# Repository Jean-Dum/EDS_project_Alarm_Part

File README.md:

# EDS_project_Alarm_Project

## Motion detection alarm

## Principal Equipment

	- PIR Sensor               --> EKMC1601111 - Motion sensor 5m 94°, Panasonic
	
	- Electromechanical Buzzer --> kmtg1603 

	- Button (For alarm test)  --> https://www.elfa.se/en/tactile-switch-pts-1no-160gf-6mm-pts645sm43smtr92lfs/p/30119498?origPos=40&q=smd%20button&pos=5&origPageSize=10&track=true

	- Variable resistor (for smoke sensor) --> https://www.elfa.se/en/trimmer-potentiometer-kohm-250-mw-bi-technologies-23br1klftr/p/16432066?q=*&pos=3&origPos=255&origPageSize=10&track=true&fbclid=IwAR1p6efSrgXudRJqt7ZX97Rhud_PuTN6X5KsHpLk5Swx5VFpF2Jh6Jaqm8U
	
	- LoRa module (long range low-power wide-area network technology) --> Murata CMWX1ZZABZ

	- Smoke Sensor --> HS-131 https://www.elfa.se/en/gas-sensor-sencera-co-ltd-hs-131/p/17302706?q=smoke+detector&pos=10&origPos=23&origPageSize=100&track=true

### Desired features

The main idea is to build a system which can detect the movement of a person using a PIR sensor. This movement will trigger an alarm and communicate using LoRa to another MCU managed by our associated team. The only way of desactivate the alarm is to introduce the correct code in the second team's terminal.

The system will also include a buzzer and a test button.

### Obtained features

Our PCB is now able to detect the movements up to 4 meters away. It makes the buzzer ring and to stop it you just have to press the button on the PCB.

At the programm beginning there is 10 seconds of waiting in order to wait for the user to go away (otherwise it will disrupt the sensor calibration) during which the info LED is blinking. Then there is 10 seconds of sensor calibration, in which it makes a 40 samples average to make a reference value and makes the LED blinking faster.

Then the programm runs and the buzzer will ring only if the sensor value exceeds the reference value.

If the alarm is stopped by pressing the button, to reactivate it just press again the buttton, the software will again wait 10 seconds to let the user go away to avoid the buzzer to ring immediatly and then run motion detection again. During this time the info LED is blinking again.

Our system send a '1' by serial connection when the sensor is triggered. The alarm can be turned off by serial connection if it receive a '1' but to do so you have to uncomment lines 143 to 152 and build the code again.

#### Here is a diagram of our program:

## Run project

### Hardawre

- Connect the St-Link programmer from the nucleo board to the PCB. To do so just connect the SWD pins to the programming pins of our PCB, in the same order.
- Then verify that the nucleo St-Link programmer wont programm the nucleo board but our PCB. To do so remove the St-Link programmer and nucleo board connectors and remove the connector that power the nucleo board.
- Then connect both the St-Link programmer and PCB USB to your computer.

### Software
Open a terminal
#### Packages installation
- First of all install openocd:
> sudo apt-get install openocd
- install cargo:
> sudo apt-get install cargo
- install arm-none-eabi-gdb:
> sudo apt-get install arm-none-eabi-gdb
- Update rust tools:
> rustup update
> rustup target add thumbv7em-none-eabihf

#### Build software
> cargo build --release

#### Run software
- Clone this repo on your computer:
> git clone https://github.com/Jean-Dum/EDS_project_Alarm_Part.git
- Then go in the software directory:
> cd EDS_project_Alarm_Part/Software/
- Execute openocd software:
> openocd -f openocd.cfg
- Open a new terminal (in the same directory) and run the code:
> cargo build --release
- Now you are in the GDB interface, just type "c" and press two times enter key. You can look the code output in the openocd terminal.

## Possible Extras

If everything goes on time and we do not have any big difficulties in the project, we plan to add also some kind of smoke detector so the alarm system is more complete. 

We also thought of adding a fingerprint sensor for desactivating the alarm in the detector terminal.

## Limitations

The fact of working two groups together makes the communication between terminals harder but we dont expect any other big problem in our terminal.

The main limitation was that there few informations about Rust (and especially about the stm32L0) on internet, doing our researchs to resolve our problems was really difficult.

## Design and Electronic

We design our circuit using Kicad and testing some parts of the circuit in LTspice.  

### Some facts about the circuit
	
- Three different LEDs: one to get infos on the code execution, one for the power and one connected to the buzzer.
	
- We add a different voltage regulator (LT1117) that allows us to have 3.3v always without the need of resistors for adjustment of the output, so we reduces the space used.

- For the Smoke detector we used a potentiometer we can use for changing the output, this is because the detector can work on different environments (humidity, temperature...) and we need to adjust the potentiometer to have an ideal output.

### Layout

For the layout we tried to make the PCB as small as possible so it can fit in a small case and this way the detection system will be more inconspicuous.

All the components are on the same layer (top) but the PIR, this way we have more space and a better 'view' for the motion sensor. The connectors are all placed on the sides of the board so it is easier to use them. We tried to put the buzzer as far as possible from the MCU just incase the vibrations of the buzzer can make any damage on the small soldering pads of the MCU in a large period of time, the decoupling capacitors and sensors are placed as close as possible from the MCU.

### Testing

We did some different tests on the board before and after ordering it
- We used LTspice to make sure everything was okey
- Test for short-circuits and bad connections
- Test after soldering the MCU
- For short-circuits between pads (here we detected a problem)
- For voltage reverse to make sure all the pads were connected
- We tested the MCU by connecting it at a low current
- Test the final performance 

## Issues / Problems 

- Circuit
	- The LT1117 pins of the footprint where wrong (they were saved as if it was LM1117) so we had to make a small fix

- Layout and soldering
	- We had to apply the re-flow process twice because of a lack of flux in the first re-flow but finally applying more flux and doing the process again we managed to solder it perfect.

- Programming
	- It took us some time to manage to connect the PCB and didn't succeed to use vscode to run our code.
	- We made a mistake on the pins connection: The PA4 pin (used for the buzzer) don't generate PWM, we had to add a wire between the PA4 and PA3 pins because PA3 can generate PWM and is used for the smoke sensor, which is not used.
	- We didn't succeed to use the Lora module, by lack of time and because this one is way to complicated to use.
	- All the programming part was really complicated to realise, in fact there is not a lot of things about rust and espetially with the stm32L0 on internet, resolving our issues was a real struggle.

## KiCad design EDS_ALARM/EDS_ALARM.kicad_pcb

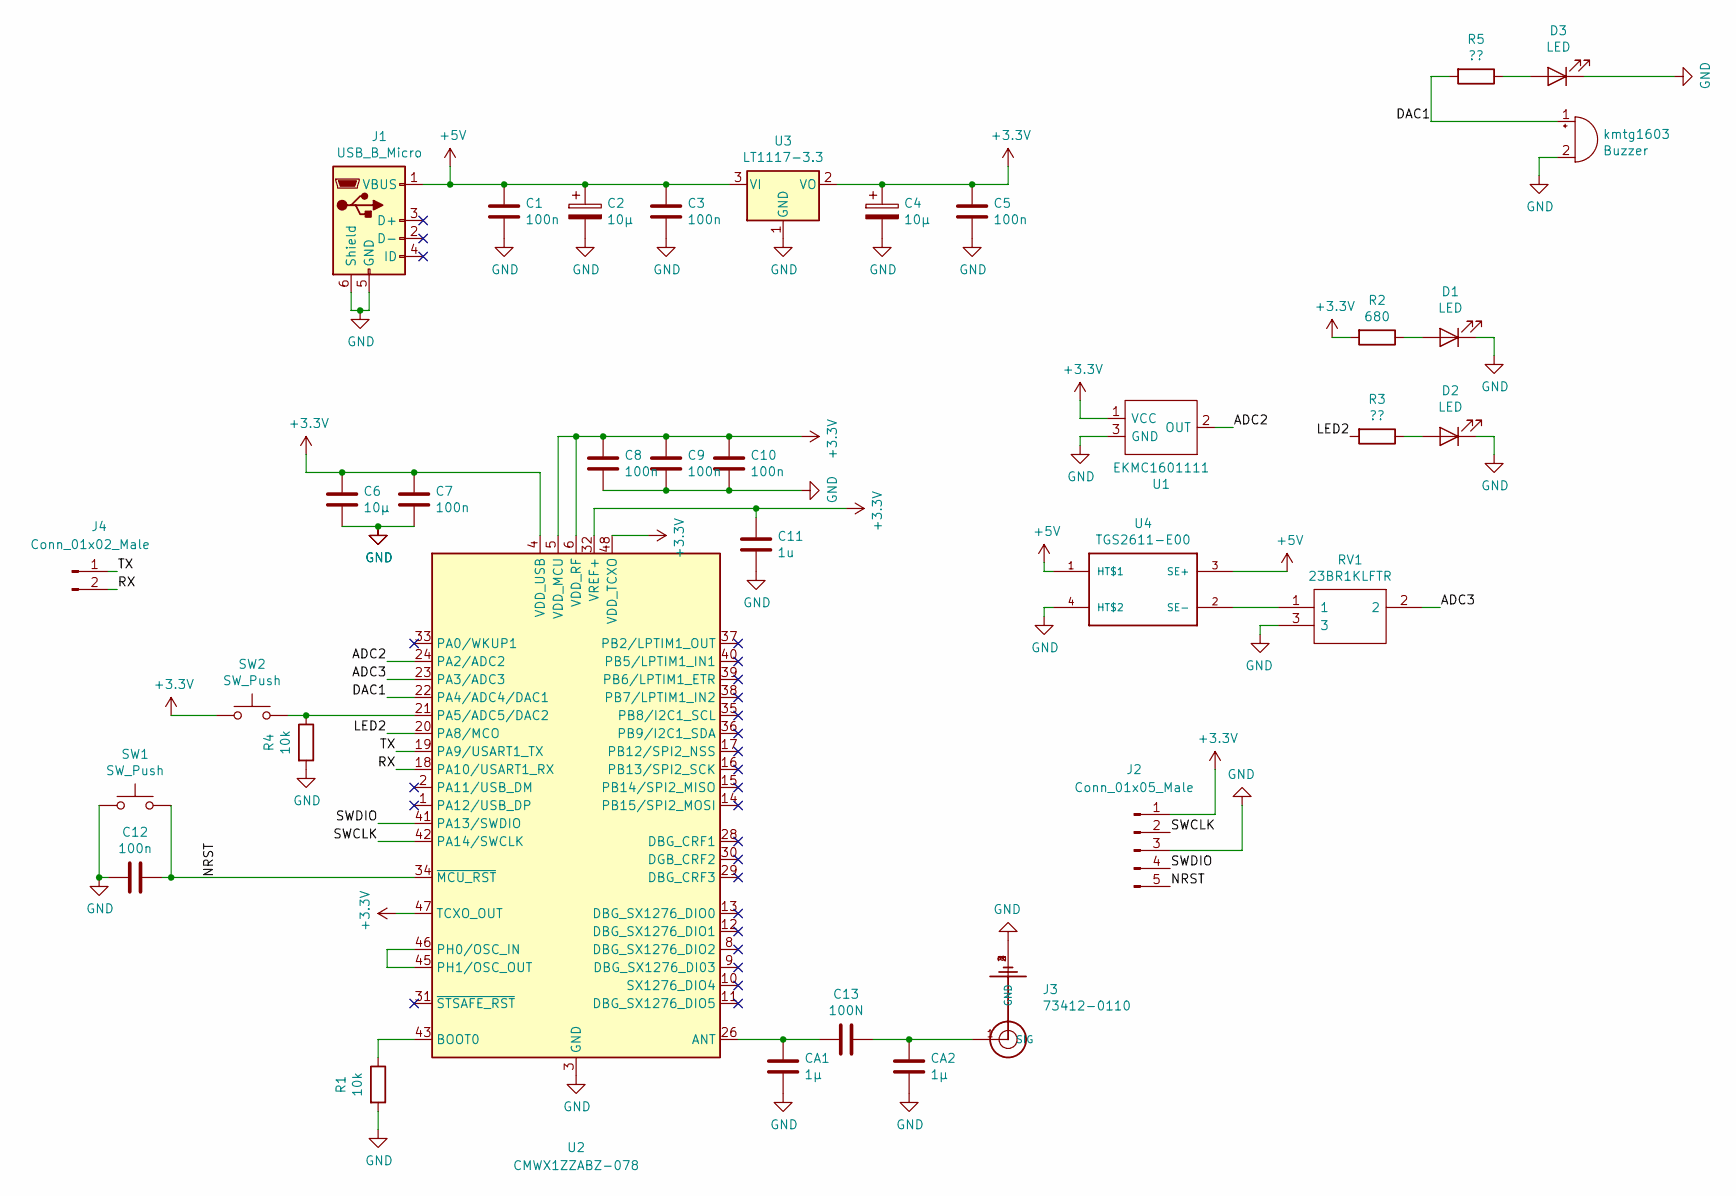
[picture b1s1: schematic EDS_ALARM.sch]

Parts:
C1, C3, C5, C7, C8, C9, C10, C12: 100n; C_0805_2012Metric_Pad1.15x1.40mm_HandSolder
C2, C4: 10µ; CP_Elec_5x4.4
C6: 10µ; C_0805_2012Metric_Pad1.15x1.40mm_HandSolder
C11: 1u; C_0805_2012Metric_Pad1.15x1.40mm_HandSolder
C13: 100N; C_0805_2012Metric_Pad1.15x1.40mm_HandSolder
CA1, CA2: 1µ; C_0805_2012Metric_Pad1.15x1.40mm_HandSolder
D1, D2, D3: LED; LED_0805_2012Metric
J1: USB_B_Micro; USB_Micro-B_Wuerth_629105150521
J2: Conn_01x05_Male; PinSocket_1x05_P2.54mm_Vertical
J3: 73412-0110; U.FL_Molex_MCRF_73412-0110_Vertical
J4: Conn_01x02_Male; PinSocket_1x02_P2.54mm_Vertical
R1, R4: 10k; R_0805_2012Metric_Pad1.15x1.40mm_HandSolder
R2: 680; R_0805_2012Metric_Pad1.15x1.40mm_HandSolder
R3, R5: ??; R_0805_2012Metric_Pad1.15x1.40mm_HandSolder
RV1: 23BR1KLFTR; 23B_1; Manufacturer_Part_Number 23BR1KLFTR; Mouser Part Number 858-23BR1KLFTR
SW1, SW2: SW_Push; SW_SPST_PTS645
U1: EKMC1601111; VZ-STANDARD; Manufacturer_Part_Number EKMC1601111; Mouser Part Number 769-EKMC1601111
U2: CMWX1ZZABZ-078; CMWX1ZZABZ_NEW
U3: LT1117-3.3; SOT-223
U4: TGS2611-E00; TGS2611C00
kmtg1603: Buzzer; KMTG16031

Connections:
+3V3: C4.1, C5.1, C6.1, C7.1, C8.1, C9.1, C10.1, C11.1, J2.1, R2.2, SW2.1, U1.1 (VCC), U2.4 (VDD_USB), U2.5 (VDD_MCU), U2.6 (VDD_RF), U2.32 (VREF+), U2.47 (TCXO_OUT), U2.48 (VDD_TCXO), U3.2 (VO)
+5V: C1.1, C2.1, C3.1, J1.1 (VBUS), U3.3 (VI), U4.1 (HT$1), U4.3 (SE+)
/ADC2: U1.2 (OUT), U2.24 (PA2/ADC2)
/ADC3: RV1.2, U2.23 (PA3/ADC3)
/DAC1: R5.2, U2.22 (PA4/ADC4/DAC1), kmtg1603.1 (-)
/LED2: R3.2, U2.20 (PA8/MCO)
/NRST: C12.1, J2.5, SW1.2, U2.34 (~MCU_RST)
/RX: J4.2, U2.18 (PA10/USART1_RX)
/SWCLK: J2.2, U2.42 (PA14/SWCLK)
/SWDIO: J2.4, U2.41 (PA13/SWDIO)
/TX: J4.1, U2.19 (PA9/USART1_TX)
GND: C1.2, C2.2, C3.2, C4.2, C5.2, C6.2, C7.2, C8.2, C9.2, C10.2, C11.2, C12.2, CA1.2, CA2.2, D1.1 (K), D2.1 (K), D3.1 (K), J1.5 (GND), J1.6 (Shield), J2.3, J3.2 (GND), J3.3 (GND), J3.4 (GND), R1.2, R4.2, RV1.3, SW1.1, U1.3 (GND), U2.3 (GND), U2.7 (GND), U2.25 (GND), U2.27 (GND), U2.44 (GND), U2.49 (GND), U2.50 (GND), U2.51 (GND), U2.52 (GND), U2.53 (GND), U2.54 (GND), U2.55 (GND), U2.56 (GND), U2.57 (GND), U3.1 (GND), U4.4 (HT$2), kmtg1603.2 (+)
unnamed: C13.1, CA2.1, J3.1 (SIG)
unnamed: C13.2, CA1.1, U2.26 (ANT)
unnamed: D1.2 (A), R2.1
unnamed: D2.2 (A), R3.1
unnamed: D3.2 (A), R5.1
unnamed: R1.1, U2.43 (BOOT0)
unnamed: R4.1, SW2.2, U2.21 (PA5/ADC5/DAC2)
unnamed: RV1.1, U4.2 (SE-)
unnamed: U2.45 (PH1/OSC_OUT), U2.46 (PH0/OSC_IN)

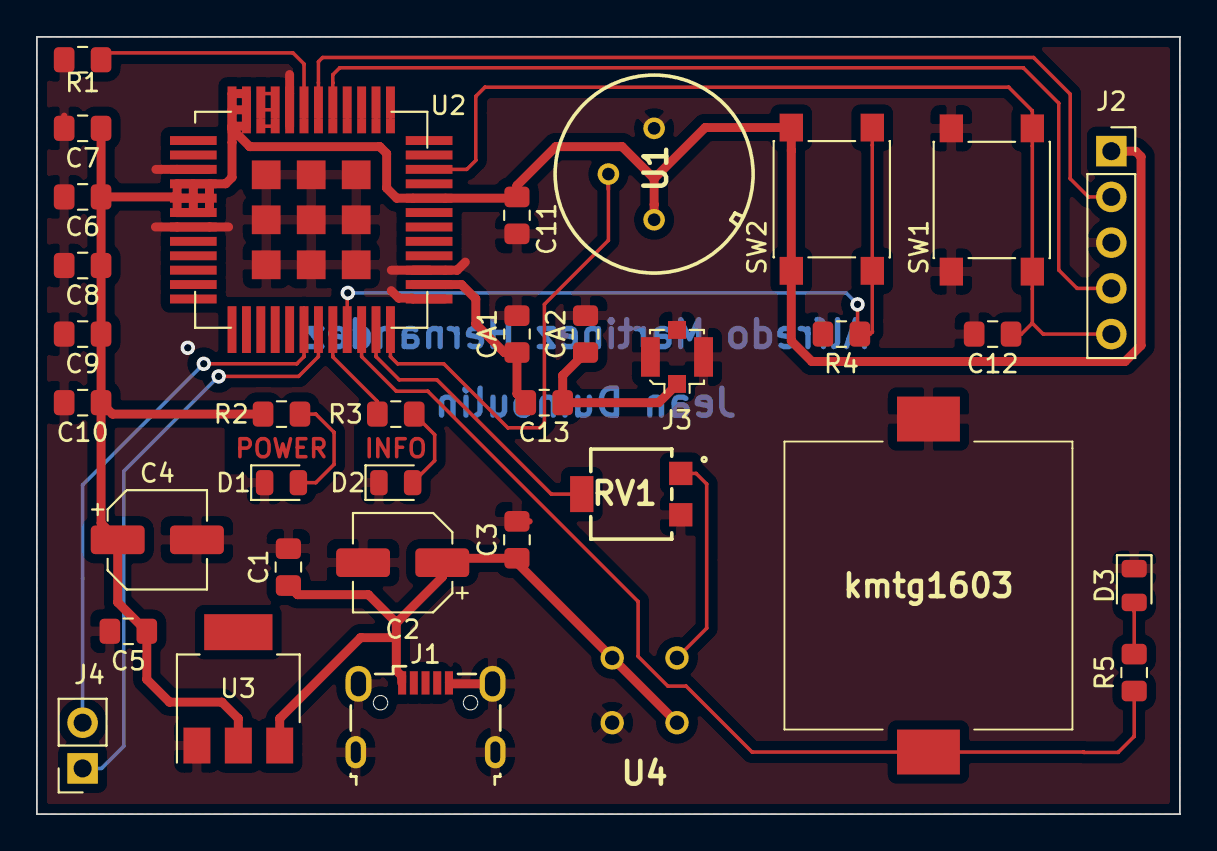
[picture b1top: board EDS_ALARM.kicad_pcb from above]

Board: 2 copper layers, 63.5 x 43.2 mm, 35 parts (0 on the bottom side), 21 nets.

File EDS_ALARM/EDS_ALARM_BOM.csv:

"Id";"Identificador";"Empaquetado";"Cantidad";"Identificación";"Suministrador y ref";
1;"C1,C3,C5,C7,C8,C9,C10,C12";"C_0805_2012Metric_Pad1.15x1.40mm_HandSolder";8;"100n";;;
2;"C2,C4";"CP_Elec_5x4.4";2;"10µ";;;
3;"C6";"C_0805_2012Metric_Pad1.15x1.40mm_HandSolder";1;"10µ";;;
4;"C11";"C_0805_2012Metric_Pad1.15x1.40mm_HandSolder";1;"1u";;;
5;"C13";"C_0805_2012Metric_Pad1.15x1.40mm_HandSolder";1;"100N";;;
6;"CA1,CA2";"C_0805_2012Metric_Pad1.15x1.40mm_HandSolder";2;"1µ";;;
7;"J1";"USB_Mini-B_Lumberg_2486_01_Horizontal";1;"USB_B_Micro";;;
8;"J2";"PinHeader_1x06_P2.54mm_Vertical";1;"Conn_01x06_Male";;;
9;"J3";"U.FL_Molex_MCRF_73412-0110_Vertical";1;"73412-0110";;;
10;"R1";"R_0805_2012Metric_Pad1.15x1.40mm_HandSolder";1;"10k";;;
11;"U2";"CMWX1ZZABZ";1;"CMWX1ZZABZ-078";;;
12;"U3";"SOT-223";1;"LT1117-3.3";;;
13;"U1";"VZ-STANDARD";1;"EKMC1601111";;;
14;"D1,D2";"LED_0805_2012Metric";2;"LED";;;
15;"RV1";"23B_1";1;"23BR1KLFTR";;;
16;"SW1";"SW_SPST_PTS645";1;"SW_Push";;;
17;"kmtg1603";"KMTG16031";1;"Buzzer";;;
18;"U4";"TGS2611C00";1;"TGS2611-E00";;;

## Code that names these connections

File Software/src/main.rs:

// Made by Jean Dumoulin and Alfredo Martinez Hernandez
// This code is meant to ring the alarm when the PIR sensor detects movement next to it

#![no_main]
#![no_std]
#![allow(non_snake_case)] 
#![deny(unsafe_code)]
#![deny(warnings)]

extern crate panic_halt;

use cortex_m_rt::entry;
use cortex_m_semihosting::{hprintln, hprint};
use stm32l0xx_hal::{self, pac, pwm, prelude::*, rcc::Config, serial};
// use nb::block; Uncomment if serial input is used

extern crate cortex_m;

#[entry]
fn main() -> ! {
    hprintln!("\nBeginning initialization").unwrap();

    let dp = pac::Peripherals::take().unwrap();
    let cp = cortex_m::Peripherals::take().unwrap();

    // Configure the clock.
    let mut rcc = dp.RCC.freeze(Config::hsi16());

    // Get the delay provider.
    let mut delay = cp.SYST.delay(rcc.clocks);

    // Acquire the GPIOA peripheral. This also enables the clock for GPIOA in the RCC register.
    let gpioa = dp.GPIOA.split(&mut rcc);

    // Configure PA8 as output (info LED output)
    let mut infoLED = gpioa.pa8.into_push_pull_output();

    // Configure PA5 as input (SW2)
    let button = gpioa.pa5.into_push_pull_output();
    
    // Configure the timer as PWM on PA3 (connected to PA4)
    let pwm = pwm::Timer::new(dp.TIM2, 1.khz(), &mut rcc);
    let mut pwm = pwm.channel4.assign(gpioa.pa3);
    let max_duty = pwm.get_max_duty() / 4095;
    pwm.enable();
    
    // Configure ADC on PA2
    let mut adc = dp.ADC.constrain(&mut rcc);
    let mut a2 = gpioa.pa2.into_analog();

    // Configure the serial peripheral on pa9 and pa10
    let tx_pin = gpioa.pa9;
    let rx_pin = gpioa.pa10;
    let serial = dp
        .USART1
        .usart((tx_pin, rx_pin), serial::Config::default(), &mut rcc)
        .unwrap();
    let (mut tx, _rx) = serial.split();

    // Initialize PIR reference value to 0
    let mut PIR_ref:u16 = 0;

    // Initialize the alarm activation boolean
    let mut alarmOnOff = true;

    // 5 seconds pause, indicates to the user that he must move away to avoid an immediate ringing
    for x in 0..10 {
        hprint!("\rWait {}s", 4 - x/2).unwrap();
        // Blink the info LED: 250ms OFF, 250ms ON
        delay.delay(250.ms());
        infoLED.set_low().unwrap();
        delay.delay(250.ms());
        infoLED.set_high().unwrap();
    }
    // Print new line
    hprintln!("").unwrap();
    // 5 seconds initialization time, makes the sum of 20 samples
    for x in 0..20 {
        hprint!("\rCalibration: {}s", 4 - x/4).unwrap();
        // Sum a PIR ADC sample
        PIR_ref = PIR_ref.wrapping_add(adc.read(&mut a2).unwrap());
        // Blink the info LED: 125ms OFF, 125ms ON
        delay.delay(125.ms());
        infoLED.set_low().unwrap();
        delay.delay(125.ms());
        infoLED.set_high().unwrap();
    }

    // Divide the result of the sum by 20, the result of the average is doubled
    let PIR_ref: u16 = PIR_ref/10;
    // Prints the average result
    hprintln!("\nReference value: {}\n", PIR_ref).unwrap();

    loop {
        // If the button is pushed
        if button.is_high().unwrap(){
            // Wait until the button is released
            while button.is_high().unwrap(){ 
                // Wait 200ms to avoid rebounce
                delay.delay(200.ms());
            }
            // Invert the alarm switch
            alarmOnOff = !alarmOnOff;
            // If the alarm is activated
            if alarmOnOff == true{
                hprintln!("\nAlarm activated").unwrap();
                // 5 seconds pause, indicates to the user that he must move away, if not it continues
                let mut temp: u8 = 0;
                loop {
                    hprint!("\rWait {}s", 9 - temp/2).unwrap();
                    // Incremet of 500ms
                    temp += 1;
                    // Blink the info LED: 250ms OFF, 250ms ON
                    delay.delay(250.ms());
                    infoLED.set_low().unwrap();
                    delay.delay(250.ms());
                    infoLED.set_high().unwrap();
                    // Take a PIR ADC sample
                    let val: u16 = adc.read(&mut a2).unwrap();
                    // If 10 seconds passed and the PIR value is less than the reference, quit the loop
                    if temp >= 20 && val < PIR_ref  {
                        break();
                    }
                    // If 10 seconds passed and the PIR value is higher than the reference, wait 5 more seconds
                    else if temp >= 20{
                        temp = 0;
                    }
                }
                hprint!("\n").unwrap();
            }
            // If the alarm is desactivated
            else {
                tx.write(0).unwrap();
                hprintln!("\nAlarm desactivated").unwrap();
                // Turn OFF the info LED
                infoLED.set_low().unwrap();
                // Set the PWM duty cycle to 0
                pwm.set_duty(max_duty * 0);
            }
        }

        // Part of the code which allows to desactivate the alarm if a '1' is received on serial port
        /*
        if block!(rx.read()).unwrap() == 1 {
            tx.write(0).unwrap();
                hprintln!("\nAlarm desactivated").unwrap();
                // Turn OFF the info LED
                infoLED.set_low().unwrap();
                // Set the PWM duty cycle to 0
                pwm.set_duty(max_duty * 0);
        }
        */

        // Get the sensor value and print it
        let val: u16 = adc.read(&mut a2).unwrap();
        hprintln!("Val:{}", val).unwrap();

        // If the alarm is activated and the PIR sensor value is higher than the reference
        if val > PIR_ref && alarmOnOff == true{
            // Set the PWM duty cycle to 2000
            pwm.set_duty(max_duty * 2000);
            hprintln!("Alarm ON").unwrap();
            // Send it on I2C
            tx.write(1).unwrap();
        }
    }
}

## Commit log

2020-01-31 Moving datasheets files in Datasheet directory
2020-01-31 Adding Kicad harware empty files
2020-01-31 Create fp-info-cache
2020-02-04 Create EDS_ALARM.sch-bak
2020-02-04 Adding PIR sensor symbol and footprint
2020-02-06 Update EDS_ALARM.sch-bak
2020-02-06 Create sym-lib-table
2020-02-10 Adding correct footprints to corresponding symbols, adding cristal
2020-02-11 Finishing schematic
2020-02-11 Finished layout
2020-02-11 Last layout modifications
2020-02-12 Layout improve
2020-02-12 Adding button, buzzer's LED
2020-02-13 MCU footprint updating
2020-03-09 Adding software directory
2020-03-09 Updating radio module code
2020-03-09 trying to fix some issues
2020-03-09 Resvolving some issues
2020-03-13 resolving some openocd issues
2020-03-20 working code: button, pwm, LED, ADC
2020-03-28 Functionning code
2020-04-01 code upgrade
2020-04-02 Resolving last issues, adding serial possibility
2020-04-02 removing build files
2020-04-02 minor changes
2020-04-03 last changes
